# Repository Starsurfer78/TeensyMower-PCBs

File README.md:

DIY Robot Lawn Mower Community: https://www.diy-robot-lawn-mower.com/

# Teensymower PCB's - DIY Robot Lawn Mower (Teensy 4.1) 

The PCB's are designed to get you started on your own robotic lawnmower project. 
It doesn't matter if you want to convert a commercial mower or use a 3D printed housing.

The TeensyMainPCB is the brain of the mower to which all sensors and motors are connected.
The PowerPCB is responsible for the power supply and monitoring of the battery and the motors. 
The Wifi SenderPCB is responsible for the perimeter cable and goes into the charging station of the mower.

For your DIY project you need all 3 Boards.

RTK GPS is not yet possible at the moment

Only a few Electronic Parts are needed. 
- JST-XH Connectors
- Screw Terminal 5.04mm
- Resistors
- Pin Header Connector 2.54mm
- Active Buzzer
- LED
- Jumper
- Teensy 4.1
- ESP32 DEV Kit V1

Attention: 
The PCB's are still under development.
If you want to order your own PCBs, please check the forum first to see if there are any problems.
Use the PCBs at your own risk, no liability is assumed.

)

Robomow RL2000:

Tianchen TC-G158:

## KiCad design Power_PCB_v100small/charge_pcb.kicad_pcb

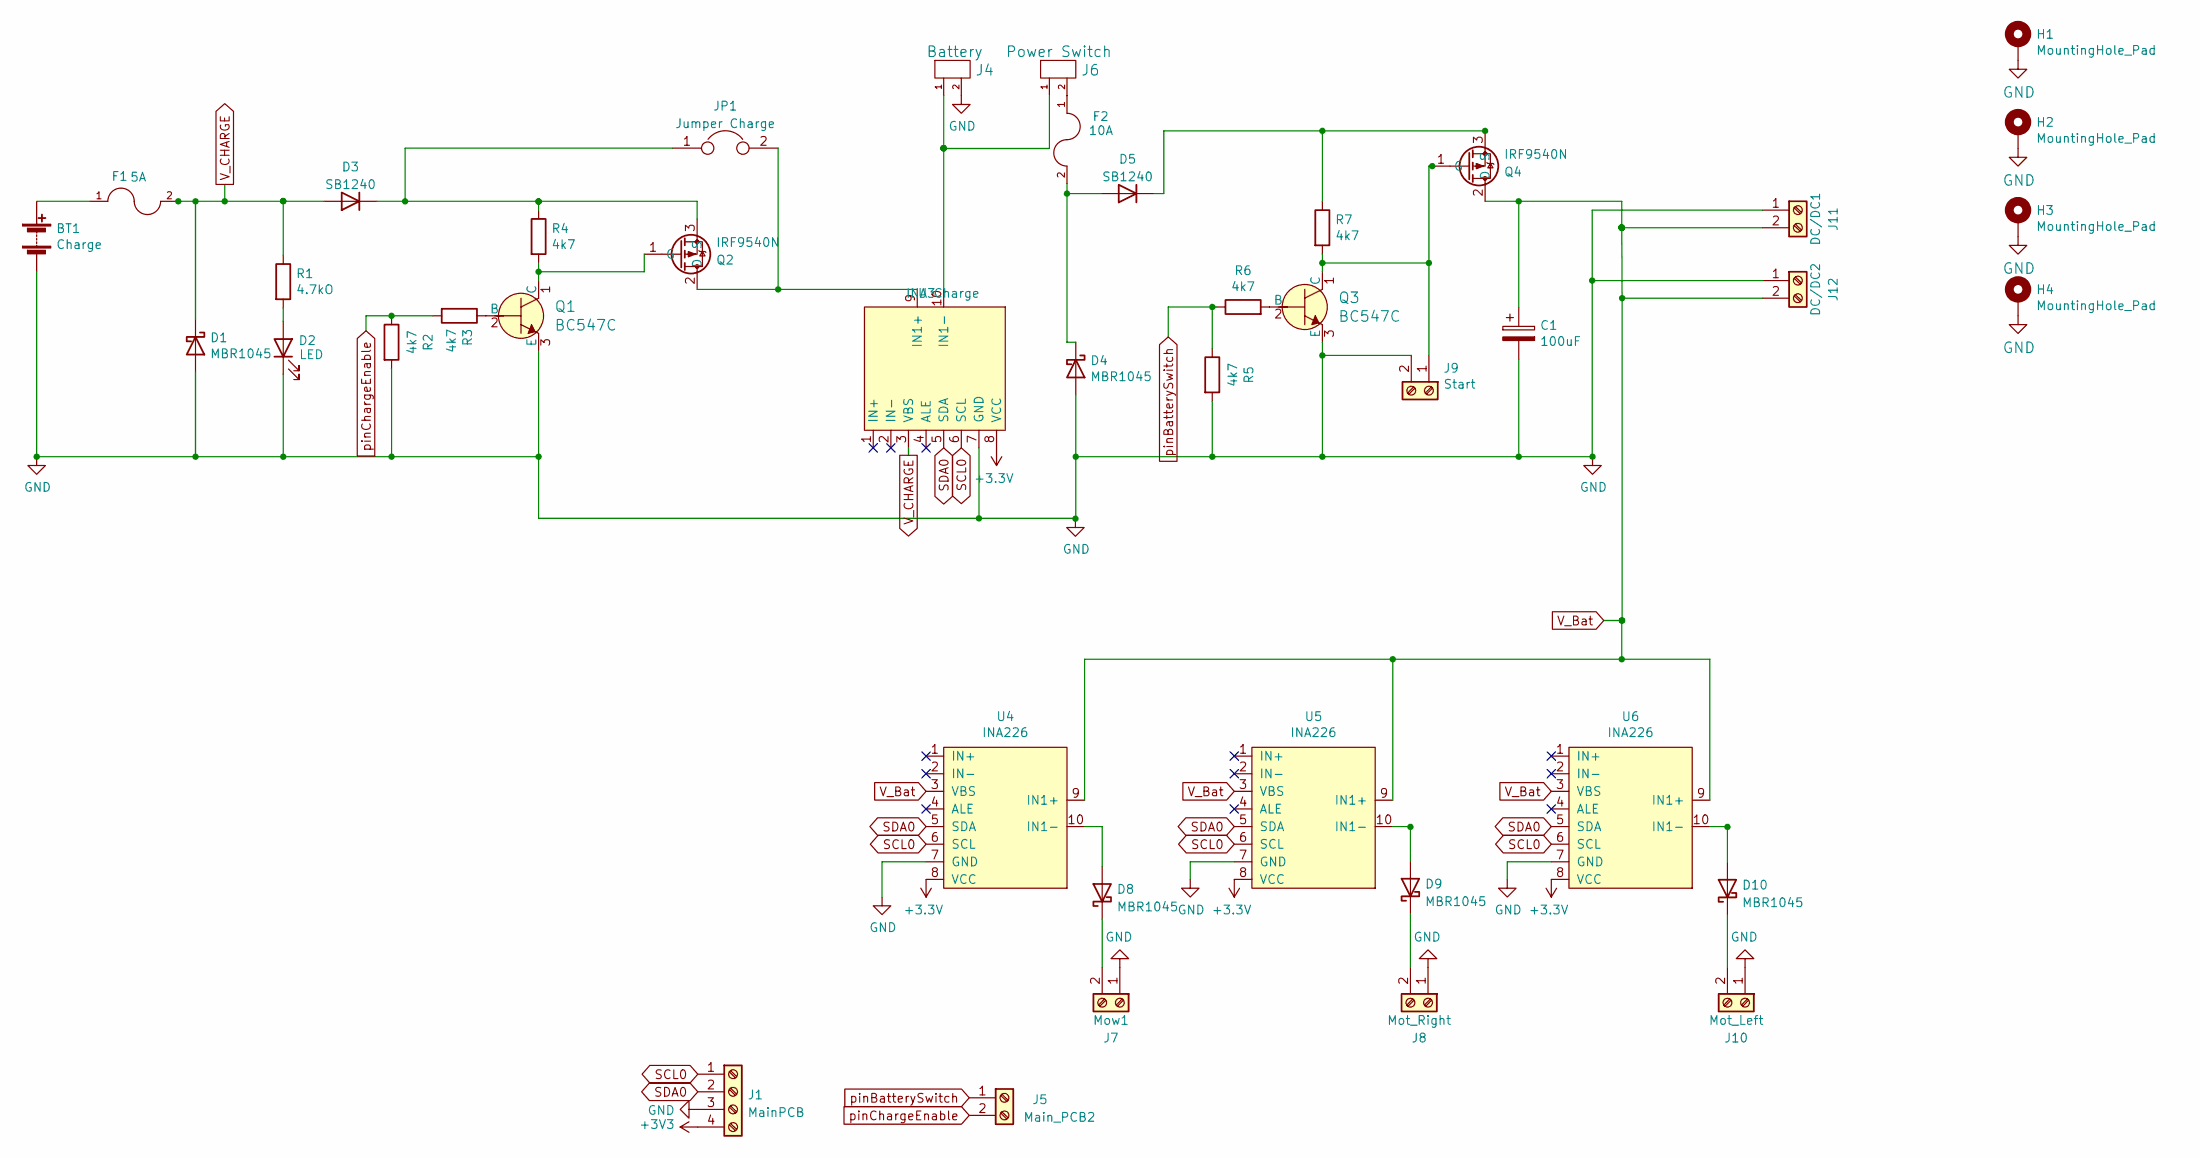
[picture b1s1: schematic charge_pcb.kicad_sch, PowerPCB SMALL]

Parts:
BT1: Charge; Anschlussklemme_2P_RM5,08
C1: 100uF; Elko_vert_11.2x6.3mm_RM2.5
D1, D4, D8, D9, D10: MBR1045; TO-220-2_Vertical
D2: LED; LED_D1.8mm_W3.3mm_H2.4mm
D3, D5: SB1240; D_DO-41_SOD81_P10.16mm_Horizontal
F1: 5A; Fuseholder_Reichelt_PL112000
F2: 10A; Fuseholder_Reichelt_PL112000
H1, H2, H3, H4: MountingHole_Pad; MountingHole_3.2mm_M3_DIN965_Pad_TopBottom
J1: MainPCB; JST_XH_B4B-XH-A_1x04_P2.50mm_Vertical
J4: Battery; TerminalBlock_bornier-2_P5.08mm
J5: Main_PCB2; JST_XH_B2B-XH-A_1x02_P2.50mm_Vertical
J6: Power Switch; TerminalBlock_bornier-2_P5.08mm
J7: Mow1; TerminalBlock_bornier-2_P5.08mm
J8: Mot_Right; TerminalBlock_bornier-2_P5.08mm
J9: Start; JST_XH_B2B-XH-A_1x02_P2.50mm_Vertical
J10: Mot_Left; TerminalBlock_bornier-2_P5.08mm
J11: DC/DC1; TerminalBlock_bornier-2_P5.08mm
J12: DC/DC2; TerminalBlock_bornier-2_P5.08mm
JP1: Jumper Charge; PinHeader_1x02_P2.54mm_Vertical
Q1, Q3: BC547C; TO-92-3_Formed_Leads; MPN BC548BTA; Digi-Key_PN BC548BTACT-ND
Q2, Q4: IRF9540N; TO-220-3_Vertical
R1: 4.7kO; R_Axial_DIN0207_L6.3mm_D2.5mm_P7.62mm_Horizontal
R2, R3, R4, R5, R6, R7: 4k7; R_Axial_DIN0207_L6.3mm_D2.5mm_P7.62mm_Horizontal
U3: INA Charge; INA226
U4, U5, U6: INA226

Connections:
GND: BT1.2 (-), C1.2, D1.2 (A), D2.1 (K), D4.2 (A), H1.1, H2.1, H3.1, H4.1, J1.3, J4.2, J7.1, J8.1, J9.2, J10.1, J11.1, J12.1, Q1.3 (E), Q3.3 (E), R2.2, R5.2, U3.7 (GND), U4.7 (GND), U5.7 (GND), U6.7 (GND)
unnamed: BT1.1 (+), F1.1
unnamed: D2.2 (A), R1.2
unnamed: D3.1 (K), JP1.1, Q2.3 (S), R4.1
unnamed: D4.1 (K), D5.2 (A), F2.2
unnamed: D5.1 (K), Q4.3 (S), R7.1
unnamed: D8.1 (K), J7.2
unnamed: D8.2 (A), U4.10 (IN1-)
unnamed: D9.1 (K), J8.2
unnamed: D9.2 (A), U5.10 (IN1-)
unnamed: D10.1 (K), J10.2
unnamed: D10.2 (A), U6.10 (IN1-)
unnamed: J4.1, J6.1, U3.10 (IN1-)
unnamed: F2.1, J6.2
unnamed: J9.1, Q3.1 (C), Q4.1 (G), R7.2
unnamed: JP1.2, Q2.2 (D), U3.9 (IN1+)
unnamed: Q1.1 (C), Q2.1 (G), R4.2
unnamed: Q1.2 (B), R3.1
unnamed: Q3.2 (B), R6.2
SCL0: J1.1, U3.6 (SCL), U4.6 (SCL), U5.6 (SCL), U6.6 (SCL)
SDA0: J1.2, U3.5 (SDA), U4.5 (SDA), U5.5 (SDA), U6.5 (SDA)
V_Bat: C1.1, J11.2, J12.2, Q4.2 (D), U4.3 (VBS), U4.9 (IN1+), U5.3 (VBS), U5.9 (IN1+), U6.3 (VBS), U6.9 (IN1+)
V_CHARGE: D1.1 (K), D3.2 (A), F1.2, R1.1, U3.3 (VBS)
pinBatterySwitch: J5.1, R5.1, R6.1
pinChargeEnable: J5.2, R2.1, R3.2

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
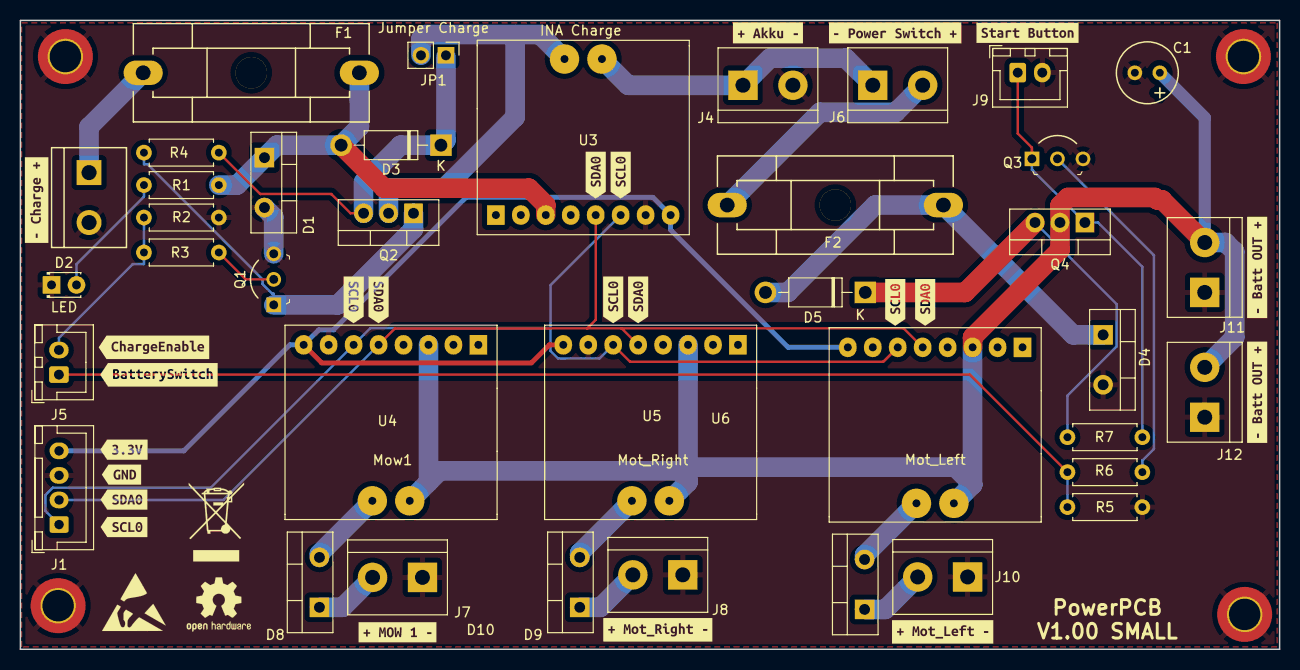
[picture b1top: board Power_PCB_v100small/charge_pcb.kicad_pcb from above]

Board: 2 copper layers, 128.1 x 64.0 mm, 65 parts (0 on the bottom side), 26 nets.

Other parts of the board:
kibuzzard-62B75E62: G***; kibuzzard-62B75E62
kibuzzard-62B75EB1: G***; kibuzzard-62B75EB1
kibuzzard-65C504B9: G***; kibuzzard-65C504B9
kibuzzard-65C5049A: G***; kibuzzard-65C5049A
kibuzzard-630F6B1E: G***; kibuzzard-630F6B1E
kibuzzard-630F6B3C: G***; kibuzzard-630F6B3C
kibuzzard-630F6FC9: G***; kibuzzard-630F6FC9
kibuzzard-630F68E0: G***; kibuzzard-630F68E0
kibuzzard-630F70A7: G***; kibuzzard-630F70A7
kibuzzard-630F714A: G***; kibuzzard-630F714A
kibuzzard-630F6257: G***; kibuzzard-630F6257
kibuzzard-630F6901: G***; kibuzzard-630F6901
kibuzzard-630F6915: G***; kibuzzard-630F6915
kibuzzard-630F6938: G***; kibuzzard-630F6938
kibuzzard-630F7110: G***; kibuzzard-630F7110
kibuzzard-630FA3ED: G***; kibuzzard-630FA3ED
kibuzzard-630FA50E: G***; kibuzzard-630FA50E
kibuzzard-630FA52F: G***; kibuzzard-630FA52F
kibuzzard-630FA55C: G***; kibuzzard-630FA55C
kibuzzard-630FA420: G***; kibuzzard-630FA420
kibuzzard-630FA573: G***; kibuzzard-630FA573
kibuzzard-6311B784: G***; kibuzzard-6311B784
kibuzzard-6311B799: G***; kibuzzard-6311B799

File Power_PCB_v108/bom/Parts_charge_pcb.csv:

ID;Bezeichner;Gehäuse;Stückzahl;Bezeichnung;Anbieter und Referenz
1;BT1;Anschlussklemme_2P_RM5,08;1;Charge;
2;C1;Elko_vert_11.2x6.3mm_RM2.5;1;100uF;
3;D1,D4;TO-220-2_Vertical;2;MBR1045;
4;F1;Fuseholder_Reichelt_PL112000;1;5A;
5;F2;Fuseholder_Reichelt_PL112000;1;10A;
6;J1;TerminalBlock_bornier-2_P5.08mm;1;Mow3;
7;Q1,Q3;TO-92-3_Formed_Leads;2;BC547C;
8;R3,R4,R5,R6,R7,R2;R_Axial_DIN0207_L6.3mm_D2.5mm_P7.62mm_Horizontal;6;4k7;
10;J8;TerminalBlock_bornier-2_P5.08mm;1;Mot_Right;
11;Q4,Q2;TO-220-3_Vertical;2;IRF9540N;
12;J2;JST_XH_B6B-XH-A_1x06_P2.50mm_Vertical;1;Main_PCB1;
13;J3;TerminalBlock_bornier-2_P5.08mm;1;Mow2;
14;J4;TerminalBlock_bornier-2_P5.08mm;1;Battery;
15;J5;JST_XH_B2B-XH-A_1x02_P2.50mm_Vertical;1;Main_PCB2;
16;J6;TerminalBlock_bornier-2_P5.08mm;1;Power Switch;
17;J7;TerminalBlock_bornier-2_P5.08mm;1;Mow1;
18;J9;JST_XH_B2B-XH-A_1x02_P2.50mm_Vertical;1;Start;
19;J10;TerminalBlock_bornier-2_P5.08mm;1;Mot_Left;
20;J11;TerminalBlock_bornier-2_P5.08mm;1;DC/DC1;
21;J12;TerminalBlock_bornier-2_P5.08mm;1;DC/DC2;
22;U2,U3,U4,U5,U6,U1;INA226;6;INA226;
23;R1;R_Axial_DIN0207_L6.3mm_D2.5mm_P7.62mm_Horizontal;1;4.7kO;
24;JP1;PinHeader_1x02_P2.54mm_Vertical;1;Jumper Charge;
25;D2;LED_D1.8mm_W3.3mm_H2.4mm;1;LED;
26;D5,D3;D_DO-41_SOD81_P10.16mm_Horizontal;2;SB1240;

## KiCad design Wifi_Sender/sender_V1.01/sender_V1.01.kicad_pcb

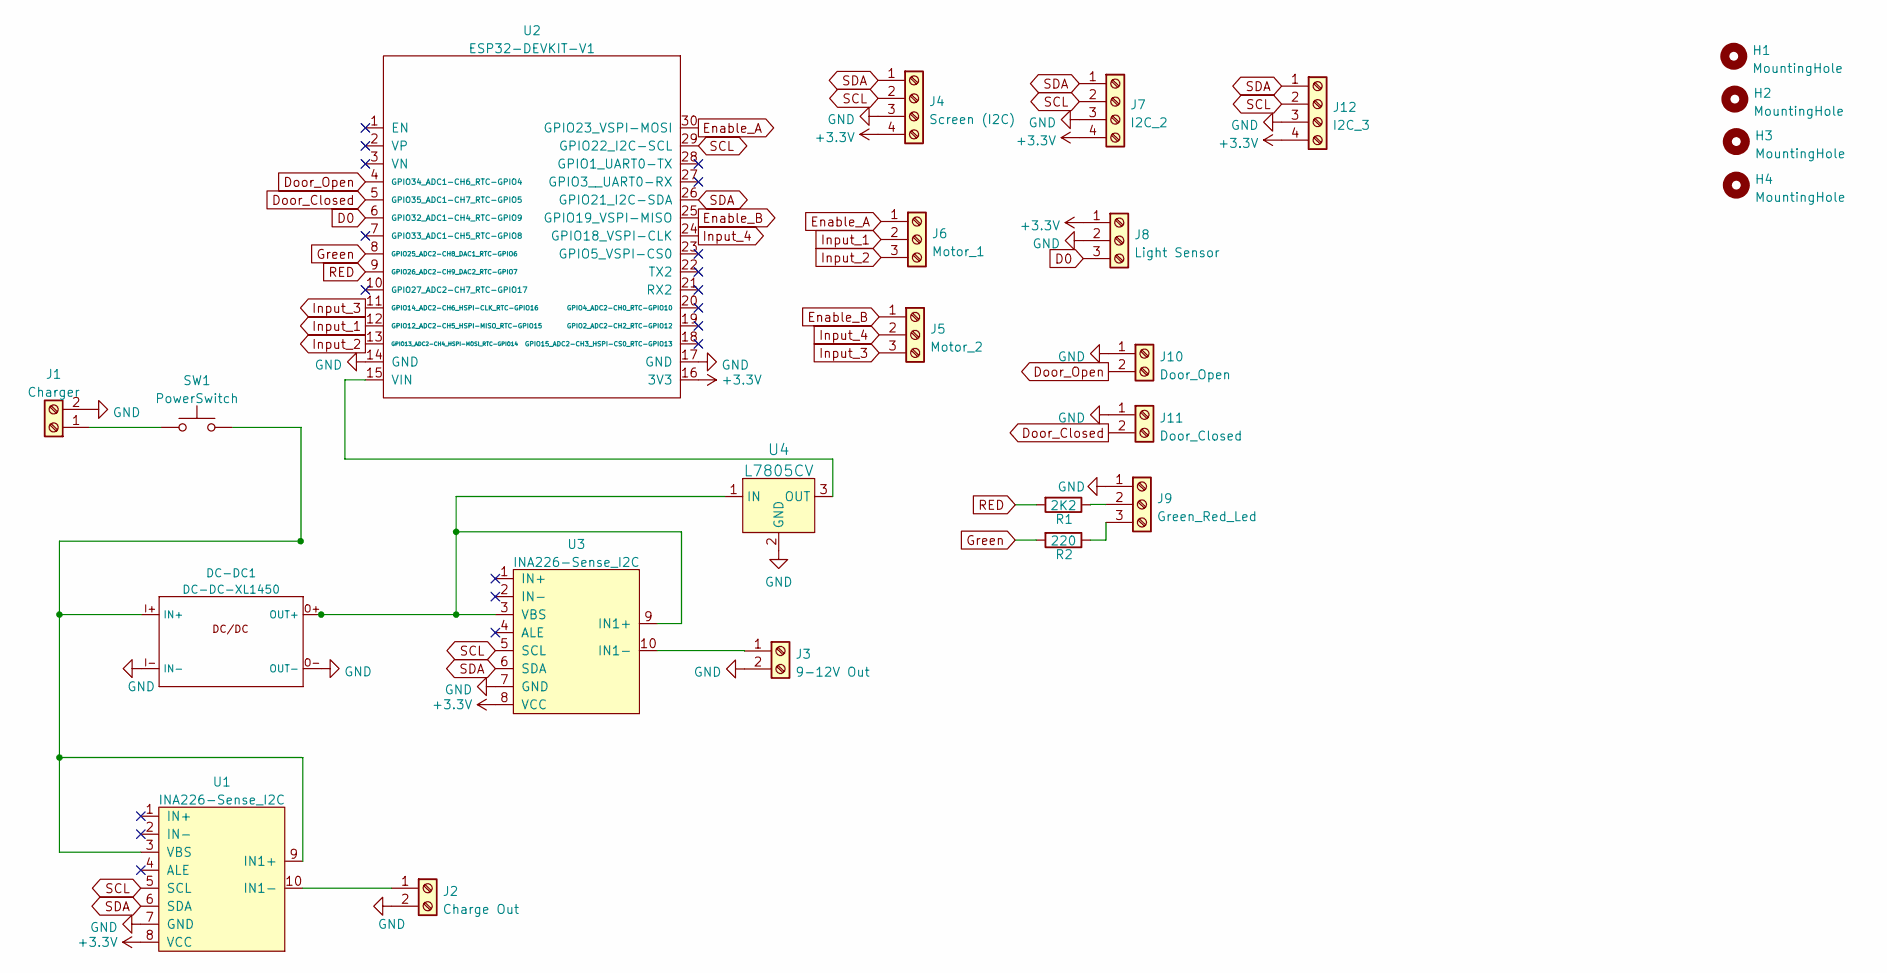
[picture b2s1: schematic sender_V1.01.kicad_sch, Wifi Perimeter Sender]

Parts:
DC-DC1: DC-DC-XL1450; DCDC-XL1450
H1, H2, H3, H4: MountingHole; MountingHole_3.2mm_M3
J1: Charger; PhoenixContact_MSTBVA_2,5_2-G-5,08_1x02_P5.08mm_Vertical
J2: Charge Out; PhoenixContact_MSTBVA_2,5_2-G-5,08_1x02_P5.08mm_Vertical
J3: 9-12V Out; PhoenixContact_MSTBVA_2,5_2-G-5,08_1x02_P5.08mm_Vertical
J4: Screen (I2C); JST_XH_B4B-XH-A_1x04_P2.50mm_Vertical
J5: Motor_2; JST_XH_B3B-XH-A_1x03_P2.50mm_Vertical
J6: Motor_1; JST_XH_B3B-XH-A_1x03_P2.50mm_Vertical
J7: I2C_2; JST_XH_B4B-XH-A_1x04_P2.50mm_Vertical
J8: Light Sensor; JST_XH_B3B-XH-A_1x03_P2.50mm_Vertical
J9: Green_Red_Led; JST_XH_B3B-XH-A_1x03_P2.50mm_Vertical
J10: Door_Open; JST_XH_B2B-XH-A_1x02_P2.50mm_Vertical
J11: Door_Closed; JST_XH_B2B-XH-A_1x02_P2.50mm_Vertical
J12: I2C_3; JST_XH_B4B-XH-A_1x04_P2.50mm_Vertical
R1: 2K2; R_Axial_DIN0207_L6.3mm_D2.5mm_P10.16mm_Horizontal
R2: 220; R_Axial_DIN0207_L6.3mm_D2.5mm_P10.16mm_Horizontal
SW1: PowerSwitch; PinHeader_1x02_P2.54mm_Vertical
U1, U3: INA226-Sense_I2C; INA226
U2: ESP32-DEVKIT-V1
U4: L7805CV; TO-220-3; MPN L7805CV; Digi-Key_PN 497-1443-5-ND

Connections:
+3V3: J4.4, J7.4, J8.1, J12.4, U1.8 (VCC), U2.16 (3V3), U3.8 (VCC)
D0: J8.3, U2.6 (GPIO32_ADC1-CH4_RTC-GPIO9)
Door_Closed: J11.2, U2.5 (GPIO35_ADC1-CH7_RTC-GPIO5)
Door_Open: J10.2, U2.4 (GPIO34_ADC1-CH6_RTC-GPIO4)
Enable_A: J6.1, U2.30 (GPIO23_VSPI-MOSI)
Enable_B: J5.1, U2.25 (GPIO19_VSPI-MISO)
GND: DC-DC1.I- (IN-), DC-DC1.O- (OUT-), J1.2, J2.2, J3.2, J4.3, J7.3, J8.2, J9.1, J10.1, J11.1, J12.3, U1.7 (GND), U2.14 (GND), U2.17 (GND), U3.7 (GND), U4.2 (GND)
Green: R2.2, U2.8 (GPIO25_ADC2-CH8_DAC1_RTC-GPIO6)
Input_1: J6.2, U2.12 (GPIO12_ADC2-CH5_HSPI-MISO_RTC-GPIO15)
Input_2: J6.3, U2.13 (GPIO13_ADC2-CH4_HSPI-MOSI_RTC-GPIO14)
Input_3: J5.3, U2.11 (GPIO14_ADC2-CH6_HSPI-CLK_RTC-GPIO16)
Input_4: J5.2, U2.24 (GPIO18_VSPI-CLK)
unnamed: DC-DC1.I+ (IN+), SW1.2, U1.3 (VBS), U1.9 (IN1+)
unnamed: DC-DC1.O+ (OUT+), U3.3 (VBS), U3.9 (IN1+), U4.1 (IN)
unnamed: J1.1, SW1.1
unnamed: J2.1, U1.10 (IN1-)
unnamed: J3.1, U3.10 (IN1-)
unnamed: J9.2, R1.1
unnamed: J9.3, R2.1
unnamed: U2.15 (VIN), U4.3 (OUT)
RED: R1.2, U2.9 (GPIO26_ADC2-CH9_DAC2_RTC-GPIO7)
SCL: J4.2, J7.2, J12.2, U1.5 (SCL), U2.29 (GPIO22_I2C-SCL), U3.5 (SCL)
SDA: J4.1, J7.1, J12.1, U1.6 (SDA), U2.26 (GPIO21_I2C-SDA), U3.6 (SDA)

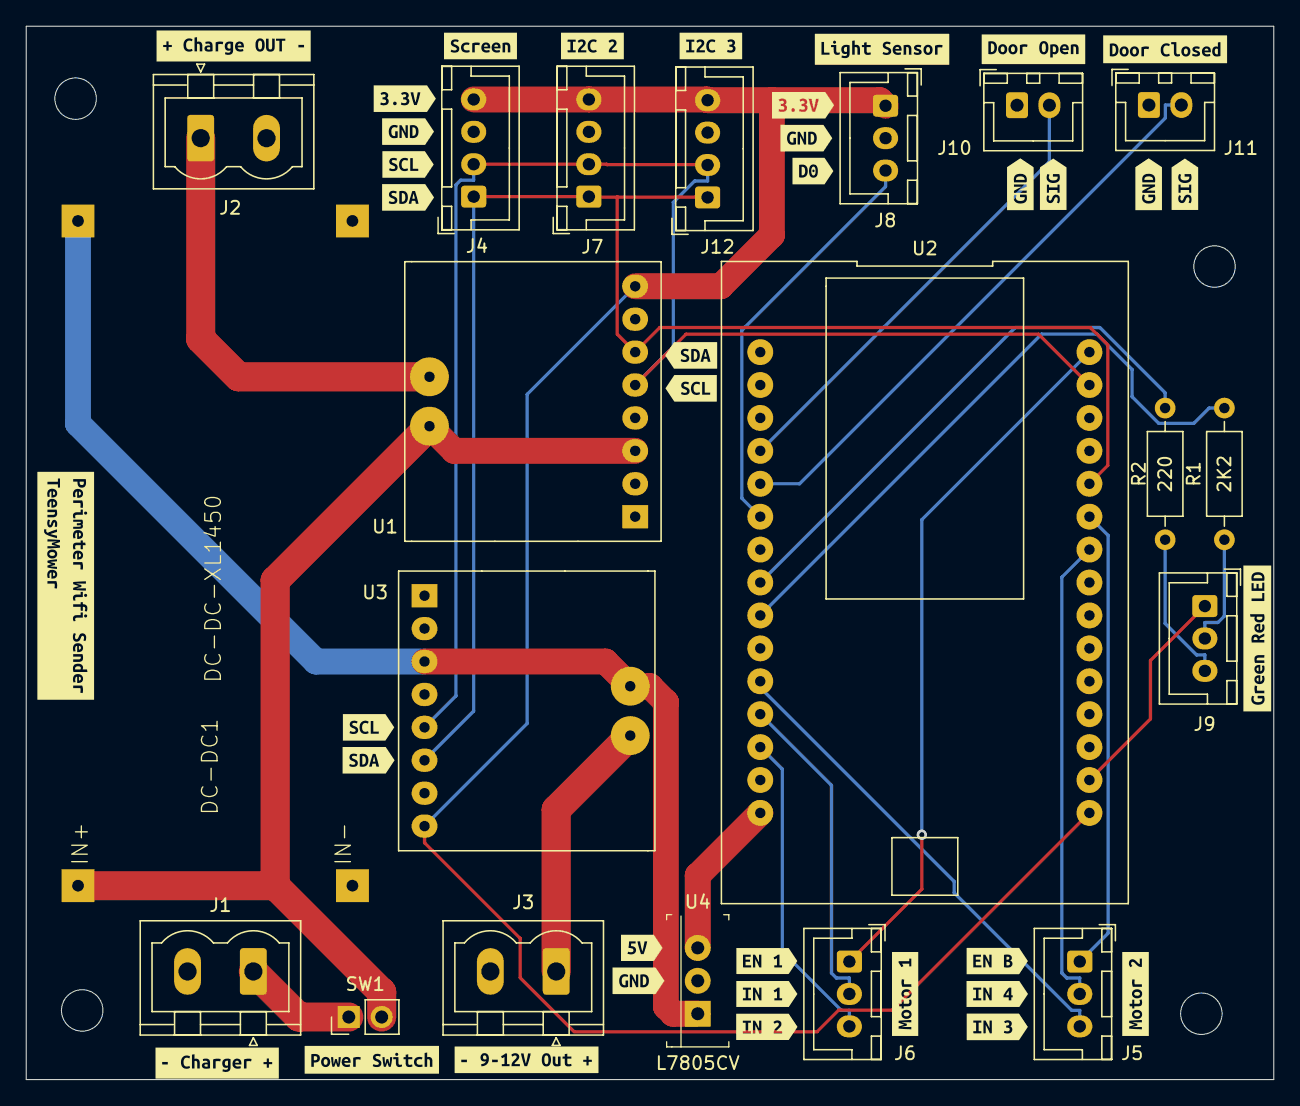
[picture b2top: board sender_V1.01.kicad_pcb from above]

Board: 2 copper layers, 96.3 x 81.3 mm, 61 parts (0 on the bottom side), 23 nets.

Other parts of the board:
kibuzzard-63A206E8: G***; kibuzzard-63A206E8
kibuzzard-63A20733: G***; kibuzzard-63A20733
kibuzzard-6384DEE7: G***; kibuzzard-6384DEE7
kibuzzard-6384DF75: G***; kibuzzard-6384DF75
kibuzzard-6384DFD2: G***; kibuzzard-6384DFD2
kibuzzard-6384E1E3: G***; kibuzzard-6384E1E3
kibuzzard-6384E1F1: G***; kibuzzard-6384E1F1
kibuzzard-6384E6A4: G***; kibuzzard-6384E6A4
kibuzzard-6384E6B7: G***; kibuzzard-6384E6B7
kibuzzard-6384E6DA: G***; kibuzzard-6384E6DA
kibuzzard-6384E6E7: G***; kibuzzard-6384E6E7
kibuzzard-6384E6FA: G***; kibuzzard-6384E6FA
kibuzzard-6384E007: G***; kibuzzard-6384E007
kibuzzard-6384E7AB: G***; kibuzzard-6384E7AB
kibuzzard-6384E7D3: G***; kibuzzard-6384E7D3
kibuzzard-6384E7EC: G***; kibuzzard-6384E7EC
kibuzzard-6384E8E9: G***; kibuzzard-6384E8E9
kibuzzard-6384E22C: G***; kibuzzard-6384E22C
kibuzzard-6384E78E: G***; kibuzzard-6384E78E
kibuzzard-6384E79B: G***; kibuzzard-6384E79B
kibuzzard-6384E93F: G***; kibuzzard-6384E93F
kibuzzard-6384E95B: G***; kibuzzard-6384E95B
kibuzzard-6384E151: G***; kibuzzard-6384E151
kibuzzard-6384E173: G***; kibuzzard-6384E173
kibuzzard-6384E189: G***; kibuzzard-6384E189
kibuzzard-6384E214: G***; kibuzzard-6384E214
kibuzzard-6384E652: G***; kibuzzard-6384E652
kibuzzard-6384E711: G***; kibuzzard-6384E711
kibuzzard-6384E779: G***; kibuzzard-6384E779
kibuzzard-6384E802: G***; kibuzzard-6384E802
kibuzzard-6384E847: G***; kibuzzard-6384E847
kibuzzard-6384E870: G***; kibuzzard-6384E870
kibuzzard-6384E880: G***; kibuzzard-6384E880
kibuzzard-6384E924: G***; kibuzzard-6384E924
kibuzzard-6384E969: G***; kibuzzard-6384E969
kibuzzard-642943C6: G***; kibuzzard-642943C6
kibuzzard-63696024: G***; kibuzzard-63696024

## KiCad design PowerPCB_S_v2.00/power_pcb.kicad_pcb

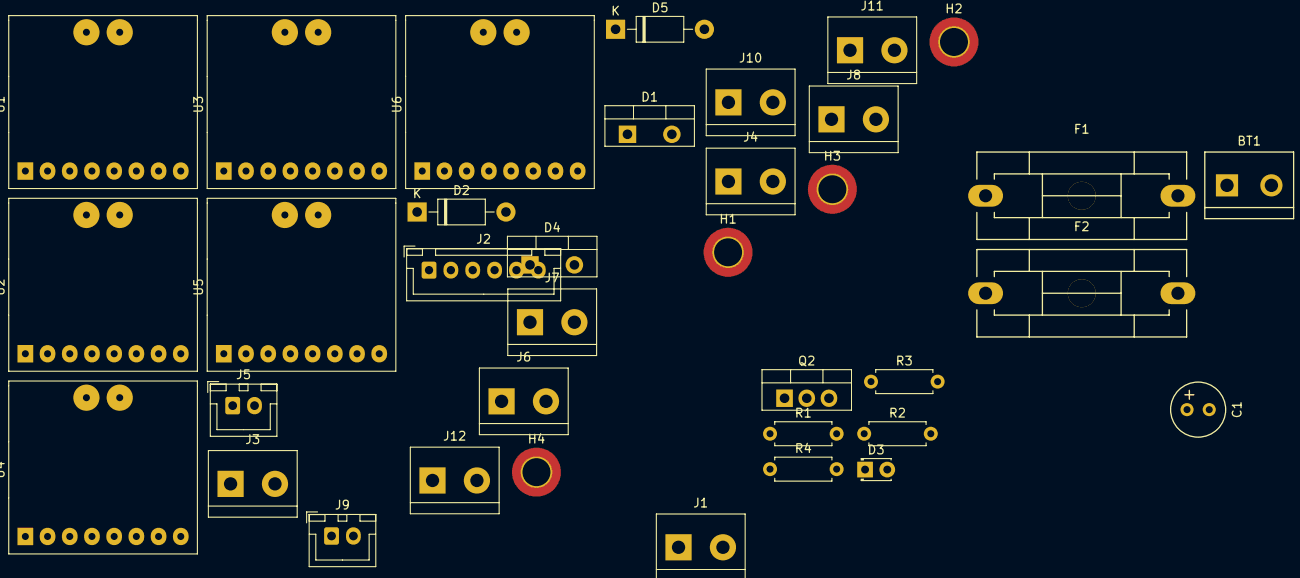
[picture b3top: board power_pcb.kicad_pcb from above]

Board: 2 copper layers, 36 parts (0 on the bottom side), 23 nets, no tracks yet.

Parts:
BT1: Charge; Anschlussklemme_2P_RM5,08
C1: 100uF; Elko_vert_11.2x6.3mm_RM2.5
D1, D4: MBR1045; TO-220-2_Vertical
D2, D5: SB1240; D_DO-41_SOD81_P10.16mm_Horizontal
D3: LED; LED_D1.8mm_W3.3mm_H2.4mm
F1: 5A; Fuseholder_Reichelt_PL112000
F2: 10A; Fuseholder_Reichelt_PL112000
H1, H2, H3, H4: MountingHole_Pad; MountingHole_3.2mm_M3_DIN965_Pad_TopBottom
J1: Mow3; TerminalBlock_bornier-2_P5.08mm
J2: Main_PCB1; JST_XH_B6B-XH-A_1x06_P2.50mm_Vertical
J3: Mow2; TerminalBlock_bornier-2_P5.08mm
J4: Battery; TerminalBlock_bornier-2_P5.08mm
J5: Main_PCB2; JST_XH_B2B-XH-A_1x02_P2.50mm_Vertical
J6: Power Switch; TerminalBlock_bornier-2_P5.08mm
J7: Mow1; TerminalBlock_bornier-2_P5.08mm
J8: Mot_Right; TerminalBlock_bornier-2_P5.08mm
J9: Start; JST_XH_B2B-XH-A_1x02_P2.50mm_Vertical
J10: Mot_Left; TerminalBlock_bornier-2_P5.08mm
J11: DC/DC2; TerminalBlock_bornier-2_P5.08mm
J12: DC/DC1; TerminalBlock_bornier-2_P5.08mm
Q2: IRF9540N; TO-220-3_Vertical
R1: 4.7kO; R_Axial_DIN0207_L6.3mm_D2.5mm_P7.62mm_Horizontal
R2, R3, R4: 4k7; R_Axial_DIN0207_L6.3mm_D2.5mm_P7.62mm_Horizontal
U1, U2, U3, U4, U5, U6: INA226

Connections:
+3V3: J2.6, U1.8 (VCC), U2.8 (VCC), U3.8 (VCC), U4.8 (VCC), U5.8 (VCC), U6.8 (VCC)
GND: BT1.2 (-), C1.2, D1.2 (A), D3.1 (K), D4.2 (A), H1.1, H2.1, H3.1, H4.1, J1.1, J2.5, J3.1, J4.2, J7.1, J8.1, J9.2, J10.1, J11.1, J12.1, R2.2, U1.7 (GND), U2.7 (GND), U3.7 (GND), U4.7 (GND), U5.7 (GND), U6.7 (GND)
unnamed: BT1.1 (+), F1.1
unnamed: C1.1, Q2.2 (D)
unnamed: D1.1 (K), D2.1 (A), F1.2
unnamed: D2.2 (K), R1.1, U3.3 (VBS), U3.9 (IN1+)
unnamed: D3.2 (A), R1.2
unnamed: D4.1 (K), D5.1 (A), F2.2
unnamed: D5.2 (K), Q2.3 (S), R4.1
unnamed: F2.1, J6.2
unnamed: J1.2, U1.10 (IN1-)
unnamed: J3.2, U2.10 (IN1-)
unnamed: J4.1, J6.1, U3.10 (IN1-)
unnamed: J7.2, U4.10 (IN1-)
unnamed: J8.2, U5.10 (IN1-)
unnamed: J9.1, Q2.1 (G), R4.2
unnamed: J10.2, U6.10 (IN1-)
SCL0: J2.3, U3.5 (SCL), U5.5 (SCL), U6.5 (SCL)
SCL1: J2.1, U1.5 (SCL), U2.5 (SCL), U4.5 (SCL)
SDA0: J2.4, U3.6 (SDA), U5.6 (SDA), U6.6 (SDA)
SDA1: J2.2, U1.6 (SDA), U2.6 (SDA), U4.6 (SDA)
V_Bat: J11.2, J12.2, U1.3 (VBS), U1.9 (IN1+), U2.3 (VBS), U2.9 (IN1+), U4.3 (VBS), U4.9 (IN1+), U5.3 (VBS), U5.9 (IN1+), U6.3 (VBS), U6.9 (IN1+)
pinBatterySwitch: J5.1, R2.1, R3.1

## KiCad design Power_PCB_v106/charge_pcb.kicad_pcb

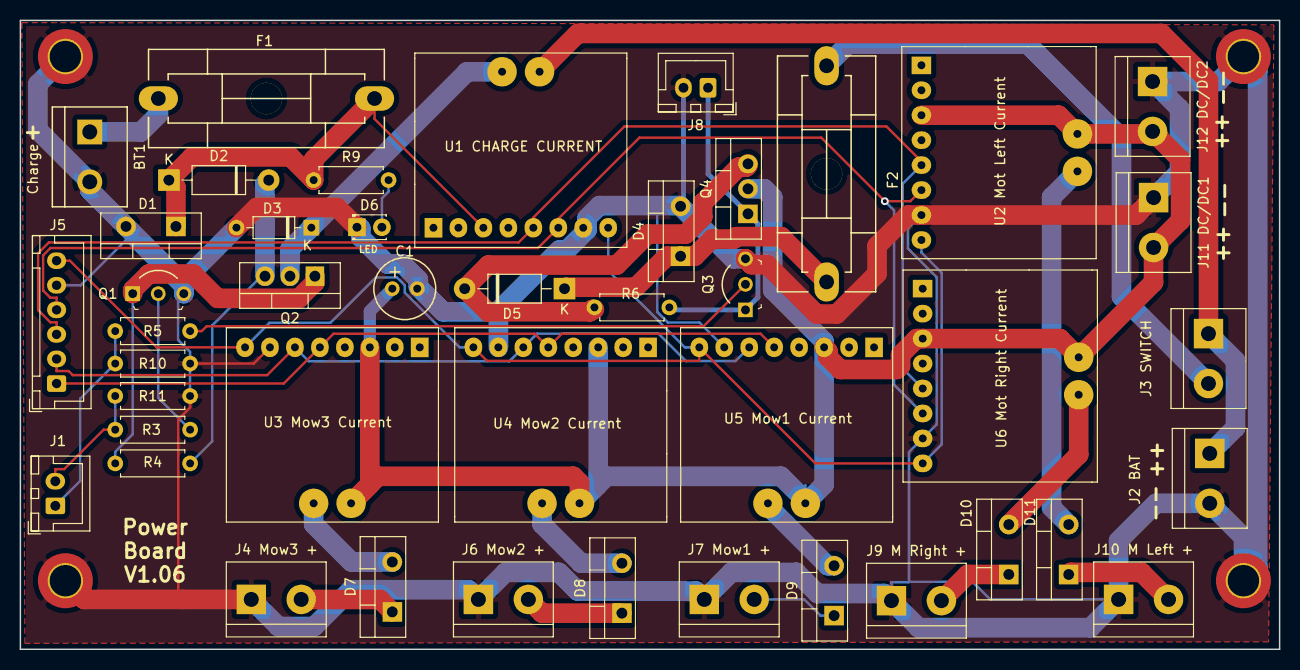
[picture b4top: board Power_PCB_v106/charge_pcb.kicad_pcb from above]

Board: 2 copper layers, 128.1 x 64.0 mm, 48 parts (0 on the bottom side), 32 nets.

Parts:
BT1: Charge; Anschlussklemme_2P_RM5,08
C1: 100uF; Elko_vert_11.2x6.3mm_RM2.5
D1, D4, D7, D8, D9, D10, D11: MBR1045; TO-220-2_Vertical
D2, D5: SB1240; D_DO-41_SOD81_P10.16mm_Horizontal
D3: 1N4148; D_DO-35_SOD27_P7.62mm_Horizontal
D6: LED; LED_D1.8mm_W3.3mm_H2.4mm
F1: 5A; Fuseholder_Reichelt_PL112000
F2: 10A; Fuseholder_Reichelt_PL112000
H1, H2, H3, H4: MountingHole_Pad; MountingHole_3.2mm_M3_DIN965_Pad_TopBottom
J1: Main_PCB2; JST_XH_B2B-XH-A_1x02_P2.50mm_Vertical
J2 BAT: Battery; TerminalBlock_bornier-2_P5.08mm
J3 SWITCH: Power Switch; TerminalBlock_bornier-2_P5.08mm
J4 Mow3 +: Mow3; TerminalBlock_bornier-2_P5.08mm
J5: Main_PCB1; JST_XH_B6B-XH-A_1x06_P2.50mm_Vertical
J6 Mow2 +: Mow2; TerminalBlock_bornier-2_P5.08mm
J7 Mow1 +: Mow1; TerminalBlock_bornier-2_P5.08mm
J8: Start; JST_XH_B2B-XH-A_1x02_P2.50mm_Vertical
J9 M Right +: Mot_Right; TerminalBlock_bornier-2_P5.08mm
J10 M Left +: Mot_Left; TerminalBlock_bornier-2_P5.08mm
J11 DC/DC1: DC/DC1; TerminalBlock_bornier-2_P5.08mm
J12 DC/DC2: DC/DC2; TerminalBlock_bornier-2_P5.08mm
Q1, Q3: BC547C; TO-92-3_Formed_Leads
Q2, Q4: IRF9540N; TO-220-3_Vertical
R3, R4, R5, R6: 4k7; R_Axial_DIN0207_L6.3mm_D2.5mm_P7.62mm_Horizontal
R9: 4.7kO; R_Axial_DIN0207_L6.3mm_D2.5mm_P7.62mm_Horizontal
R10, R11: 2k2; R_Axial_DIN0207_L6.3mm_D2.5mm_P7.62mm_Horizontal
U1 CHARGE CURRENT, U2 Mot Left Current, U3 Mow3 Current, U4 Mow2 Current, U5 Mow1 Current, U6 Mot Right Current: INA226

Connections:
+3V3: J5.6, U1 CHARGE CURRENT.8, U2 Mot Left Current.8, U3 Mow3 Current.8, U4 Mow2 Current.8, U5 Mow1 Current.8, U6 Mot Right Current.8
GND: BT1.2, C1.2, D1.2, D3.2, D4.2, D6.1, H1.1, H2.1, H3.1, H4.1, J2 BAT.2, J4 Mow3 +.1, J5.5, J6 Mow2 +.1, J7 Mow1 +.1, J8.2, J9 M Right +.1, J10 M Left +.1, J11 DC/DC1.1, J12 DC/DC2.1, Q1.3, Q3.3, R10.2, R11.2, U1 CHARGE CURRENT.7, U2 Mot Left Current.7, U3 Mow3 Current.7, U4 Mow2 Current.7, U5 Mow1 Current.7, U6 Mot Right Current.7
unnamed: BT1.1, F1.1
unnamed: D2.2, Q2.3, R4.1
unnamed: D3.1, Q2.2, U1 CHARGE CURRENT.9
unnamed: D4.1, D5.1, F2.2
unnamed: D5.2, Q4.3, R6.1
unnamed: D6.2, R9.2
unnamed: D7.1, J4 Mow3 +.2
unnamed: D7.2, U3 Mow3 Current.10
unnamed: D8.1, J6 Mow2 +.2
unnamed: D8.2, U4 Mow2 Current.10
unnamed: D9.1, J7 Mow1 +.2
unnamed: D9.2, U5 Mow1 Current.10
unnamed: D10.1, J9 M Right +.2
unnamed: D10.2, U6 Mot Right Current.10
unnamed: D11.1, J10 M Left +.2
unnamed: D11.2, U2 Mot Left Current.10
unnamed: F2.1, J3 SWITCH.2
unnamed: J2 BAT.1, J3 SWITCH.1, U1 CHARGE CURRENT.10
unnamed: J8.1, Q3.1, Q4.1, R6.2
unnamed: Q1.1, Q2.1, R4.2
unnamed: Q1.2, R3.1
unnamed: Q3.2, R5.2
SCL0: J5.3, U1 CHARGE CURRENT.5, U2 Mot Left Current.5, U6 Mot Right Current.5
SCL1: J5.1, U3 Mow3 Current.5, U4 Mow2 Current.5, U5 Mow1 Current.5
SDA0: J5.4, U1 CHARGE CURRENT.6, U2 Mot Left Current.6, U6 Mot Right Current.6
SDA1: J5.2, U3 Mow3 Current.6, U4 Mow2 Current.6, U5 Mow1 Current.6
V_Bat: C1.1, J11 DC/DC1.2, J12 DC/DC2.2, Q4.2, U2 Mot Left Current.3, U2 Mot Left Current.9, U3 Mow3 Current.3, U3 Mow3 Current.9, U4 Mow2 Current.3, U4 Mow2 Current.9, U5 Mow1 Current.3, U5 Mow1 Current.9, U6 Mot Right Current.3, U6 Mot Right Current.9
V_Charge: D1.1, D2.1, F1.2, R9.1, U1 CHARGE CURRENT.3
pinBatterySwitch: J1.1, R5.1, R10.1
pinChargeEnable: J1.2, R3.2, R11.1
